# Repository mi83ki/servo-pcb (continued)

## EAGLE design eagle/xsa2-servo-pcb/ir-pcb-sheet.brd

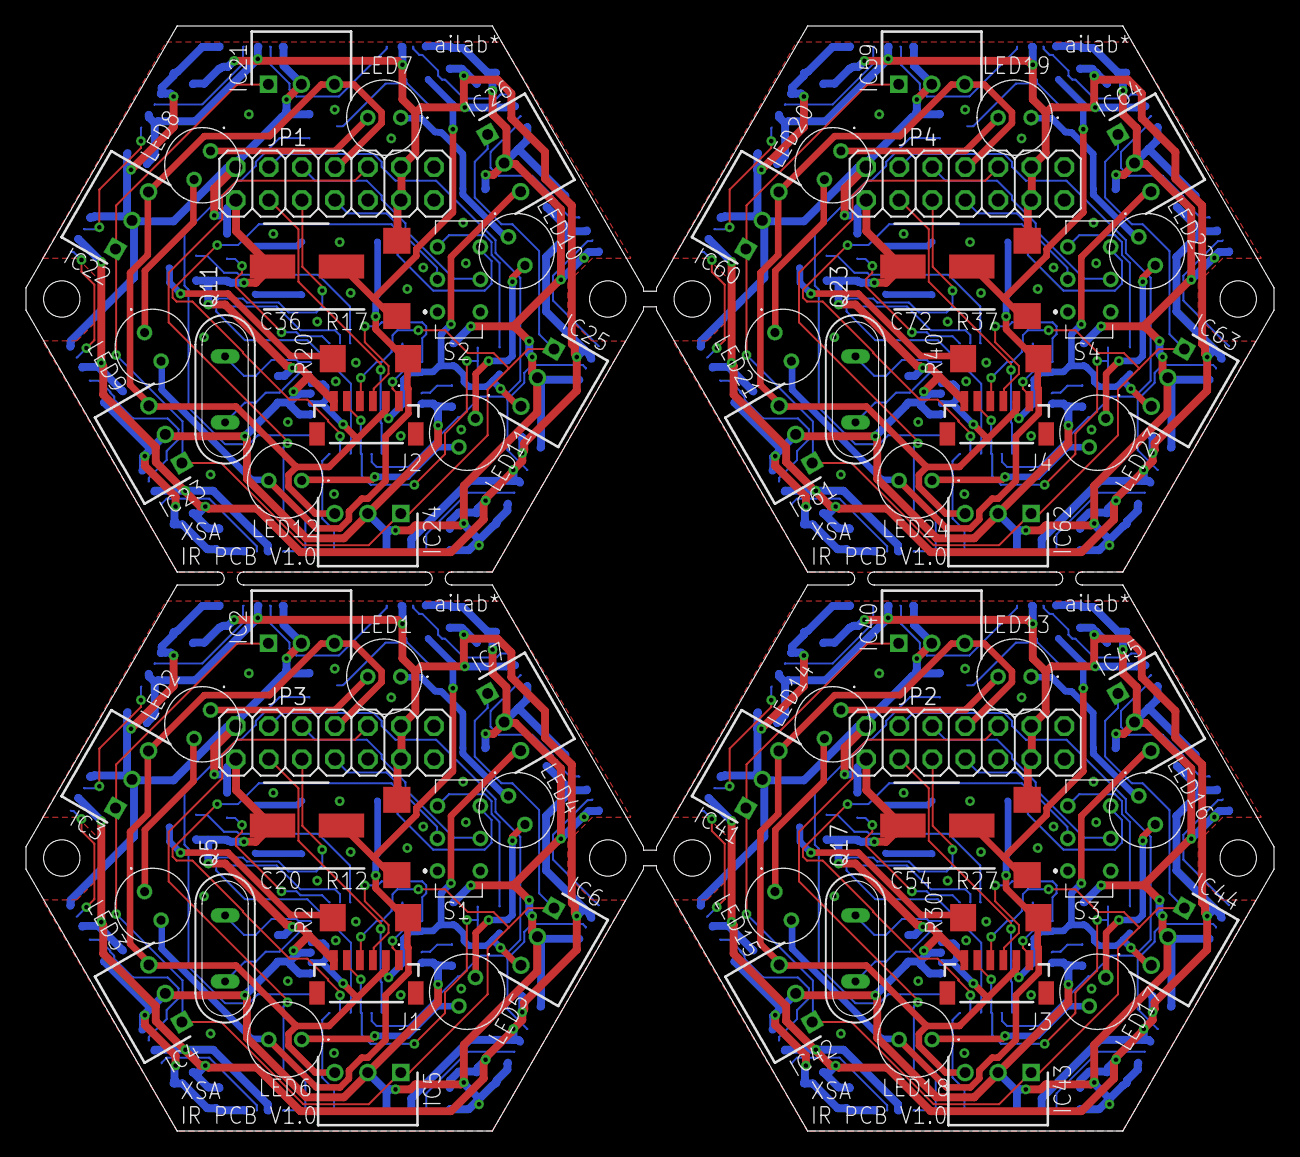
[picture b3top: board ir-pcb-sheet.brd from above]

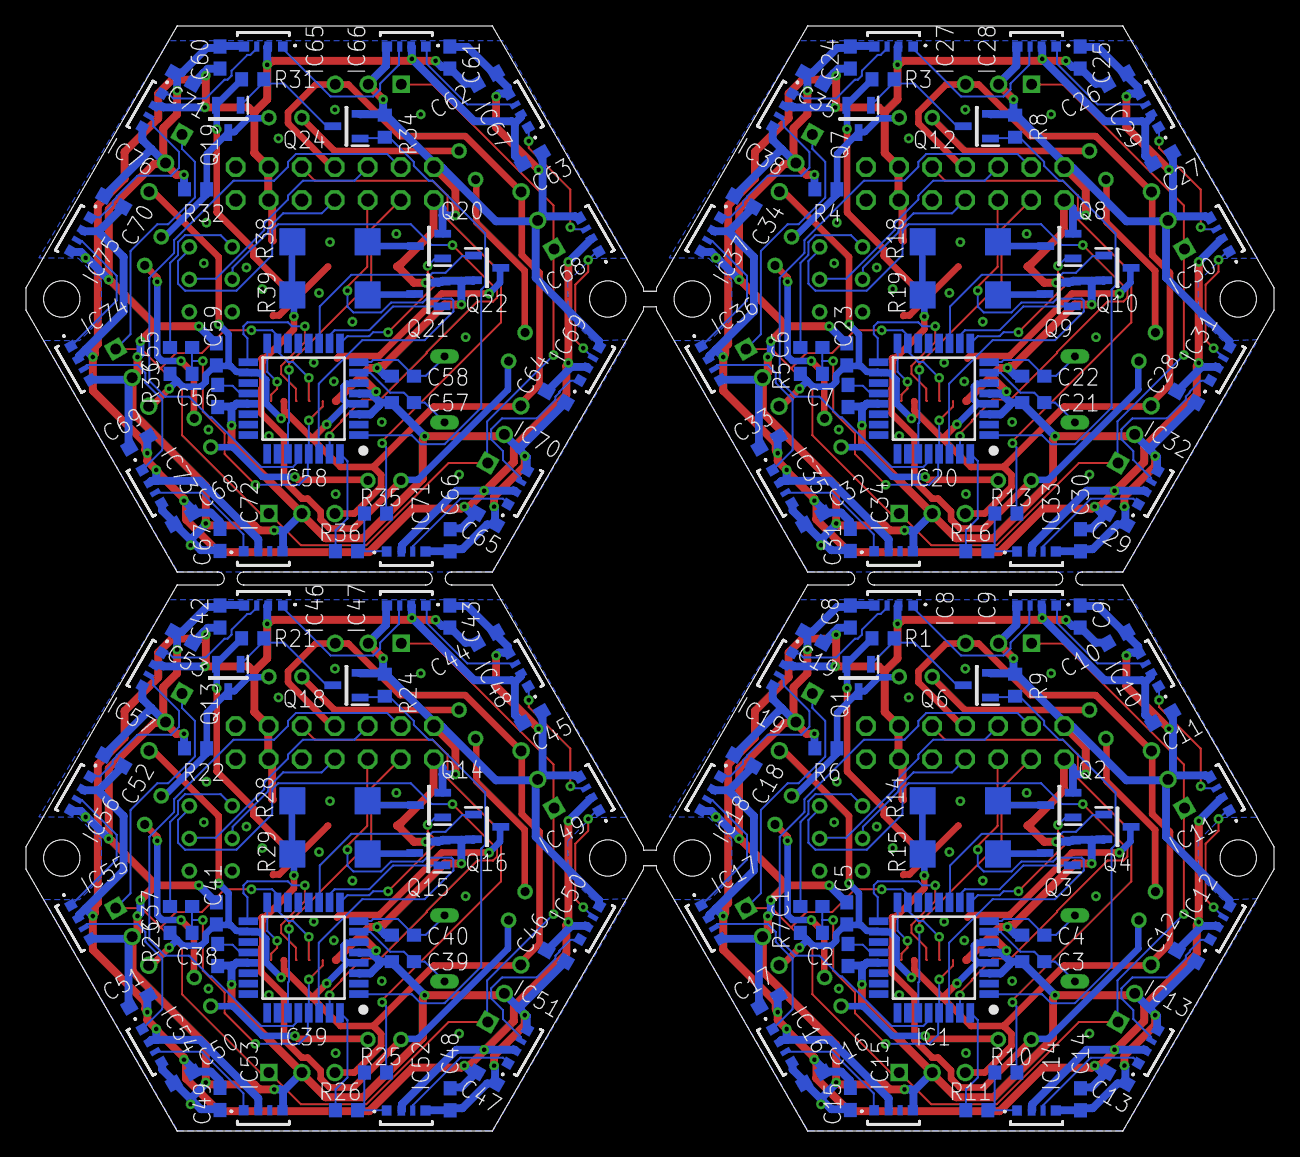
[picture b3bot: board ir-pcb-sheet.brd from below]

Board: 2 copper layers, 96.0 x 85.0 mm, 248 parts (172 on the bottom side), 184 nets.

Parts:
C1, C2, C5, C6, C7, C8, C9, C10, C11, C12, C13, C14, C15, C16, C17, C18, C19, C23, C24, C25, C26, C27, C28, C29, C30, C31, C32, C33, C34, C35, C37, C38, C41, C42, C43, C44, C45, C46, C47, C48, C49, C50, C51, C52, C53, C55, C56, C59, C60, C61, C62, C63, C64, C65, C66, C67, C68, C69, C70, C71: 0.1u; C0603
C3, C4, C21, C22, C39, C40, C57, C58: 22p; C0603
C20, C36, C54, C72: 25PFV100M6.3X8; CAPAE660X800N
IC1, IC20, IC39, IC58: ATMEGA328P-AU; QFP80P900X900X120-32N
IC2, IC3, IC4, IC5, IC6, IC7, IC21, IC22, IC23, IC24, IC25, IC26, IC40, IC41, IC42, IC43, IC44, IC45, IC59, IC60, IC61, IC62, IC63, IC64: PL-IRM0101; TO254P525X740X825-3P
IC8, IC9, IC10, IC11, IC12, IC13, IC14, IC15, IC16, IC17, IC18, IC19, IC27, IC28, IC29, IC30, IC31, IC32, IC33, IC34, IC35, IC36, IC37, IC38, IC46, IC47, IC48, IC49, IC50, IC51, IC52, IC53, IC54, IC55, IC56, IC57, IC65, IC66, IC67, IC68, IC69, IC70, IC71, IC72, IC73, IC74, IC75, IC76: SK6812_SIDE; SK6812SIDE
J1, J2, J3, J4: BM06B-SRSS-TBT_LF__SN_; BM06BSRSSTBTLFSN
JP1, JP2, JP3, JP4: Stacking Connector; 2X07
LED1, LED2, LED3, LED4, LED5, LED6, LED7, LED8, LED9, LED10, LED11, LED12, LED13, LED14, LED15, LED16, LED17, LED18, LED19, LED20, LED21, LED22, LED23, LED24: OSI5FU5111C-40; OSI5FU5111C40
Q1, Q7, Q13, Q19: IRLML6402; SOT95P237X112-3N
Q2, Q3, Q4, Q6, Q8, Q9, Q10, Q12, Q14, Q15, Q16, Q18, Q20, Q21, Q22, Q24: IRFML8244; SOT95P237X112-3N
Q5, Q11, Q17, Q23: 8MHz; QS
R1, R3, R4, R6, R8, R9, R21, R22, R24, R31, R32, R34: 1k; R0603
R2, R20, R30, R40: 39; R2512W
R5, R7, R23, R33: 10k; R0603
R10, R11, R13, R16, R25, R26, R35, R36: 0; R0603
R12, R17, R27, R37: 1; R2512W
R14, R18, R28, R38: 2; R2512W
R15, R19, R29, R39: 10; R2512W
S1, S2, S3, S4: IS-2235; IS2235

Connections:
+3V1: C23.2, IC20.4, IC20.6, IC20.18, IC21.3, IC22.3, IC23.3, IC24.3, IC25.3, IC26.3, J2.2, JP1.8, R5.1
+3V2: C41.2, IC39.4, IC39.6, IC39.18, IC40.3, IC41.3, IC42.3, IC43.3, IC44.3, IC45.3, J3.2, JP2.8, R23.1
+3V3: C5.2, IC1.4, IC1.6, IC1.18, IC2.3, IC3.3, IC4.3, IC5.3, IC6.3, IC7.3, J1.2, JP3.8, R7.1
+3V4: C59.2, IC58.4, IC58.6, IC58.18, IC59.3, IC60.3, IC61.3, IC62.3, IC63.3, IC64.3, J4.2, JP4.8, R33.1
GND: C2.1, C3.1, C4.1, C5.1, C8.1, C9.1, C10.1, C11.1, C12.1, C13.1, C14.1, C15.1, C16.1, C17.1, C18.1, C19.1, C20.2, IC1.3, IC1.5, IC1.21, IC2.2, IC3.2, IC4.2, IC5.2, IC6.2, IC7.2, IC8.4, IC9.4, IC10.4, IC11.4, IC12.4, IC13.4, IC14.4, IC15.4, IC16.4, IC17.4, IC18.4, IC19.4, J1.6, JP3.1, JP3.2, Q2.2, Q3.2, Q4.2, Q6.2, R6.1, R9.1
GND1: C7.1, C21.1, C22.1, C23.1, C24.1, C25.1, C26.1, C27.1, C28.1, C29.1, C30.1, C31.1, C32.1, C33.1, C34.1, C35.1, C36.2, IC20.3, IC20.5, IC20.21, IC21.2, IC22.2, IC23.2, IC24.2, IC25.2, IC26.2, IC27.4, IC28.4, IC29.4, IC30.4, IC31.4, IC32.4, IC33.4, IC34.4, IC35.4, IC36.4, IC37.4, IC38.4, J2.6, JP1.1, JP1.2, Q8.2, Q9.2, Q10.2, Q12.2, R4.1, R8.1
GND2: C38.1, C39.1, C40.1, C41.1, C42.1, C43.1, C44.1, C45.1, C46.1, C47.1, C48.1, C49.1, C50.1, C51.1, C52.1, C53.1, C54.2, IC39.3, IC39.5, IC39.21, IC40.2, IC41.2, IC42.2, IC43.2, IC44.2, IC45.2, IC46.4, IC47.4, IC48.4, IC49.4, IC50.4, IC51.4, IC52.4, IC53.4, IC54.4, IC55.4, IC56.4, IC57.4, J3.6, JP2.1, JP2.2, Q14.2, Q15.2, Q16.2, Q18.2, R22.1, R24.1
GND3: C56.1, C57.1, C58.1, C59.1, C60.1, C61.1, C62.1, C63.1, C64.1, C65.1, C66.1, C67.1, C68.1, C69.1, C70.1, C71.1, C72.2, IC58.3, IC58.5, IC58.21, IC59.2, IC60.2, IC61.2, IC62.2, IC63.2, IC64.2, IC65.4, IC66.4, IC67.4, IC68.4, IC69.4, IC70.4, IC71.4, IC72.4, IC73.4, IC74.4, IC75.4, IC76.4, J4.6, JP4.1, JP4.2, Q20.2, Q21.2, Q22.2, Q24.2, R32.1, R34.1
LED1: LED1.1, LED4.1, Q1.3, R6.2
LED2: C20.1, Q1.2, R1.1, R12.1
LED3: LED4.2, LED5.1
LED4: LED1.2, LED2.1
LED5: LED5.2, LED6.1
LED6: LED2.2, LED3.1
LED7: LED3.2, LED6.2, R2.2, R14.2, R15.2
LED8: Q2.3, R14.1
LED9: Q3.3, R15.1
LED10: Q4.3, R2.1
LED11: LED7.2, LED8.1
LED12: LED8.2, LED9.1
LED13: LED10.2, LED11.1
LED14: LED11.2, LED12.1
LED15: LED7.1, LED10.1, Q7.3, R4.2
LED16: LED9.2, LED12.2, R18.2, R19.2, R20.2
LED17: Q8.3, R18.1
LED18: Q9.3, R19.1
LED19: Q10.3, R20.1
LED20: C36.1, Q7.2, R3.1, R17.1
LED21: LED13.2, LED14.1
LED22: LED14.2, LED15.1
LED23: LED16.2, LED17.1
LED24: LED17.2, LED18.1
LED25: LED13.1, LED16.1, Q13.3, R22.2
LED26: LED15.2, LED18.2, R28.2, R29.2, R30.2
LED27: Q14.3, R28.1
LED28: Q15.3, R29.1
LED29: Q16.3, R30.1
LED30: C54.1, Q13.2, R21.1, R27.1
LED31: LED19.2, LED20.1
LED32: LED20.2, LED21.1
LED33: LED22.2, LED23.1
LED34: LED23.2, LED24.1
LED35: LED19.1, LED22.1, Q19.3, R32.2
LED36: LED21.2, LED24.2, R38.2, R39.2, R40.2
LED37: Q20.3, R38.1
LED38: Q21.3, R39.1
LED39: Q22.3, R40.1
LED40: C72.1, Q19.2, R31.1, R37.1
unnamed: IC1.16, J1.1
unnamed: Q1.1, Q6.3, R1.2
unnamed: JP3.6, S1.5
unnamed: IC20.17, J2.3
unnamed: IC1.17, J1.3
unnamed: IC20.16, J2.1
unnamed: IC20.1, Q12.1, R8.2
unnamed: IC20.9, Q8.1
unnamed: IC20.10, Q9.1
unnamed: IC1.1, Q6.1, R9.2
unnamed: IC8.1, IC9.3
unnamed: IC20.11, Q10.1
unnamed: C2.2, IC1.20
unnamed: JP3.7, S1.2
unnamed: IC20.28, JP1.4
unnamed: IC20.30, JP1.5
unnamed: C7.2, IC20.20
unnamed: IC1.9, Q2.1
unnamed: IC1.10, Q3.1
unnamed: IC1.11, Q4.1
unnamed: IC1.28, JP3.4
unnamed: C3.2, IC1.7, Q5.1
unnamed: IC1.30, JP3.5
unnamed: IC13.1, IC14.3
unnamed: C1.2, IC1.29, J1.5, R7.2
unnamed: C4.2, IC1.8, Q5.2
unnamed: C21.2, IC20.7, Q11.1
unnamed: C1.1, S1.3
unnamed: IC1.31, S1.6
unnamed: IC1.27, JP3.3
unnamed: IC12.1, IC13.3
unnamed: IC11.1, IC12.3
unnamed: IC10.1, IC11.3
unnamed: IC9.1, IC10.3
unnamed: C22.2, IC20.8, Q11.2
unnamed: IC8.3, IC19.1
unnamed: IC18.1, IC19.3
unnamed: IC17.1, IC18.3
unnamed: IC16.1, IC17.3
unnamed: IC15.1, IC16.3
unnamed: IC1.15, IC2.1, IC3.1, IC4.1, IC5.1, IC6.1, IC7.1, J1.4
unnamed: JP3.10, R10.2
unnamed: IC1.32, R11.2
unnamed: IC14.1, R10.1, R11.1
unnamed: C6.2, IC20.29, J2.5, R5.2
unnamed: C6.1, S2.3
unnamed: Q7.1, Q12.3, R3.2
unnamed: IC20.27, JP1.3
unnamed: JP1.6, S2.5
unnamed: JP1.7, S2.2
unnamed: IC20.31, S2.6
unnamed: JP1.10, R13.2
unnamed: IC20.32, R16.2
unnamed: IC20.15, IC21.1, IC22.1, IC23.1, IC24.1, IC25.1, IC26.1, J2.4
unnamed: IC32.1, IC33.3
unnamed: IC31.1, IC32.3
unnamed: IC30.1, IC31.3
unnamed: IC29.1, IC30.3
unnamed: IC28.1, IC29.3
unnamed: IC33.1, R13.1, R16.1
unnamed: IC27.3, IC38.1
unnamed: IC37.1, IC38.3
unnamed: IC36.1, IC37.3
unnamed: IC35.1, IC36.3
unnamed: IC34.1, IC35.3
unnamed: IC27.1, IC28.3
unnamed: IC39.17, J3.3
unnamed: IC39.16, J3.1
unnamed: IC39.1, Q18.1, R24.2
unnamed: IC39.9, Q14.1
unnamed: IC39.10, Q15.1
unnamed: IC39.11, Q16.1
unnamed: IC39.28, JP2.4
unnamed: IC39.30, JP2.5
unnamed: C38.2, IC39.20
unnamed: C39.2, IC39.7, Q17.1
unnamed: C40.2, IC39.8, Q17.2
unnamed: C37.2, IC39.29, J3.5, R23.2
unnamed: C37.1, S3.3
unnamed: Q13.1, Q18.3, R21.2
unnamed: IC39.27, JP2.3
unnamed: JP2.6, S3.5
unnamed: JP2.7, S3.2
unnamed: IC39.31, S3.6
unnamed: JP2.10, R25.2
unnamed: IC39.32, R26.2
unnamed: IC39.15, IC40.1, IC41.1, IC42.1, IC43.1, IC44.1, IC45.1, J3.4
unnamed: IC51.1, IC52.3
unnamed: IC50.1, IC51.3
unnamed: IC49.1, IC50.3
unnamed: IC48.1, IC49.3
unnamed: IC47.1, IC48.3
unnamed: IC52.1, R25.1, R26.1
unnamed: IC46.3, IC57.1
unnamed: IC56.1, IC57.3
unnamed: IC55.1, IC56.3
unnamed: IC54.1, IC55.3
unnamed: IC53.1, IC54.3
unnamed: IC46.1, IC47.3
unnamed: IC58.17, J4.3
unnamed: IC58.16, J4.1
unnamed: IC58.1, Q24.1, R34.2
unnamed: IC58.9, Q20.1
unnamed: IC58.10, Q21.1
unnamed: IC58.11, Q22.1
unnamed: IC58.28, JP4.4
unnamed: IC58.30, JP4.5
unnamed: C56.2, IC58.20
unnamed: C57.2, IC58.7, Q23.1
unnamed: C58.2, IC58.8, Q23.2
unnamed: C55.2, IC58.29, J4.5, R33.2
unnamed: C55.1, S4.3
unnamed: Q19.1, Q24.3, R31.2
unnamed: IC58.27, JP4.3
unnamed: JP4.6, S4.5
unnamed: JP4.7, S4.2
unnamed: IC58.31, S4.6
unnamed: JP4.10, R35.2
unnamed: IC58.32, R36.2
unnamed: IC58.15, IC59.1, IC60.1, IC61.1, IC62.1, IC63.1, IC64.1, J4.4
unnamed: IC70.1, IC71.3
unnamed: IC69.1, IC70.3
unnamed: IC68.1, IC69.3
unnamed: IC67.1, IC68.3
unnamed: IC66.1, IC67.3
unnamed: IC71.1, R35.1, R36.1
unnamed: IC65.3, IC76.1
unnamed: IC75.1, IC76.3
unnamed: IC74.1, IC75.3
unnamed: IC73.1, IC74.3
unnamed: IC72.1, IC73.3
unnamed: IC65.1, IC66.3
VDD: C8.2, C9.2, C10.2, C11.2, C12.2, C13.2, C14.2, C15.2, C16.2, C17.2, C18.2, C19.2, IC8.2, IC9.2, IC10.2, IC11.2, IC12.2, IC13.2, IC14.2, IC15.2, IC16.2, IC17.2, IC18.2, IC19.2, JP3.11, JP3.12, R12.2
VDD1: C24.2, C25.2, C26.2, C27.2, C28.2, C29.2, C30.2, C31.2, C32.2, C33.2, C34.2, C35.2, IC27.2, IC28.2, IC29.2, IC30.2, IC31.2, IC32.2, IC33.2, IC34.2, IC35.2, IC36.2, IC37.2, IC38.2, JP1.11, JP1.12, R17.2
VDD2: C42.2, C43.2, C44.2, C45.2, C46.2, C47.2, C48.2, C49.2, C50.2, C51.2, C52.2, C53.2, IC46.2, IC47.2, IC48.2, IC49.2, IC50.2, IC51.2, IC52.2, IC53.2, IC54.2, IC55.2, IC56.2, IC57.2, JP2.11, JP2.12, R27.2
VDD3: C60.2, C61.2, C62.2, C63.2, C64.2, C65.2, C66.2, C67.2, C68.2, C69.2, C70.2, C71.2, IC65.2, IC66.2, IC67.2, IC68.2, IC69.2, IC70.2, IC71.2, IC72.2, IC73.2, IC74.2, IC75.2, IC76.2, JP4.11, JP4.12, R37.2

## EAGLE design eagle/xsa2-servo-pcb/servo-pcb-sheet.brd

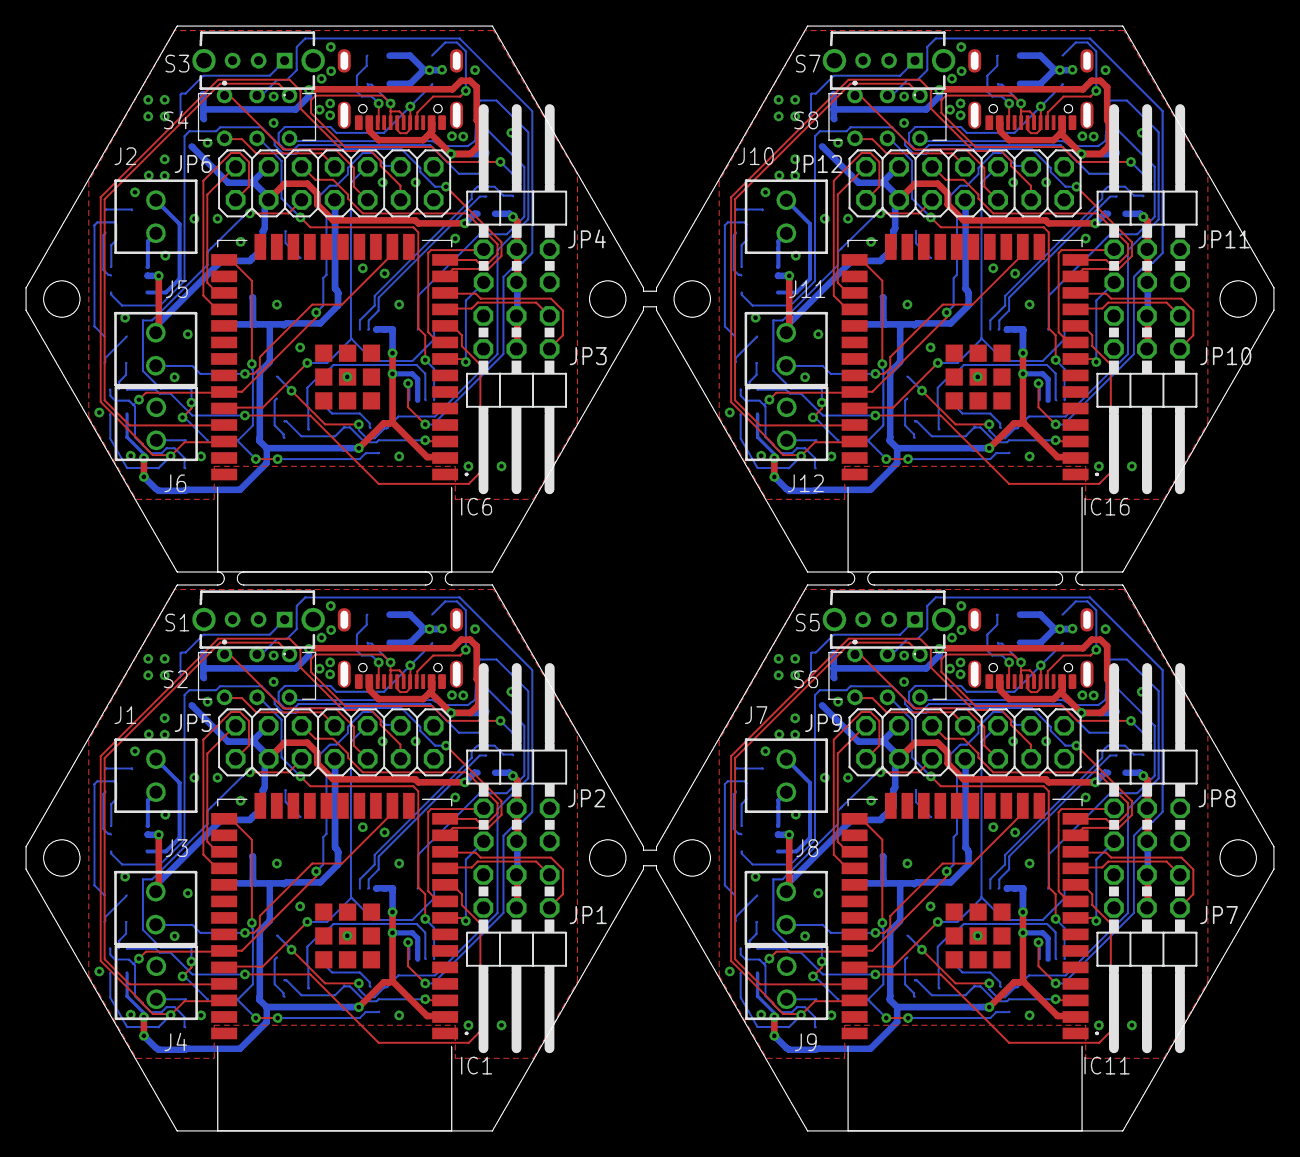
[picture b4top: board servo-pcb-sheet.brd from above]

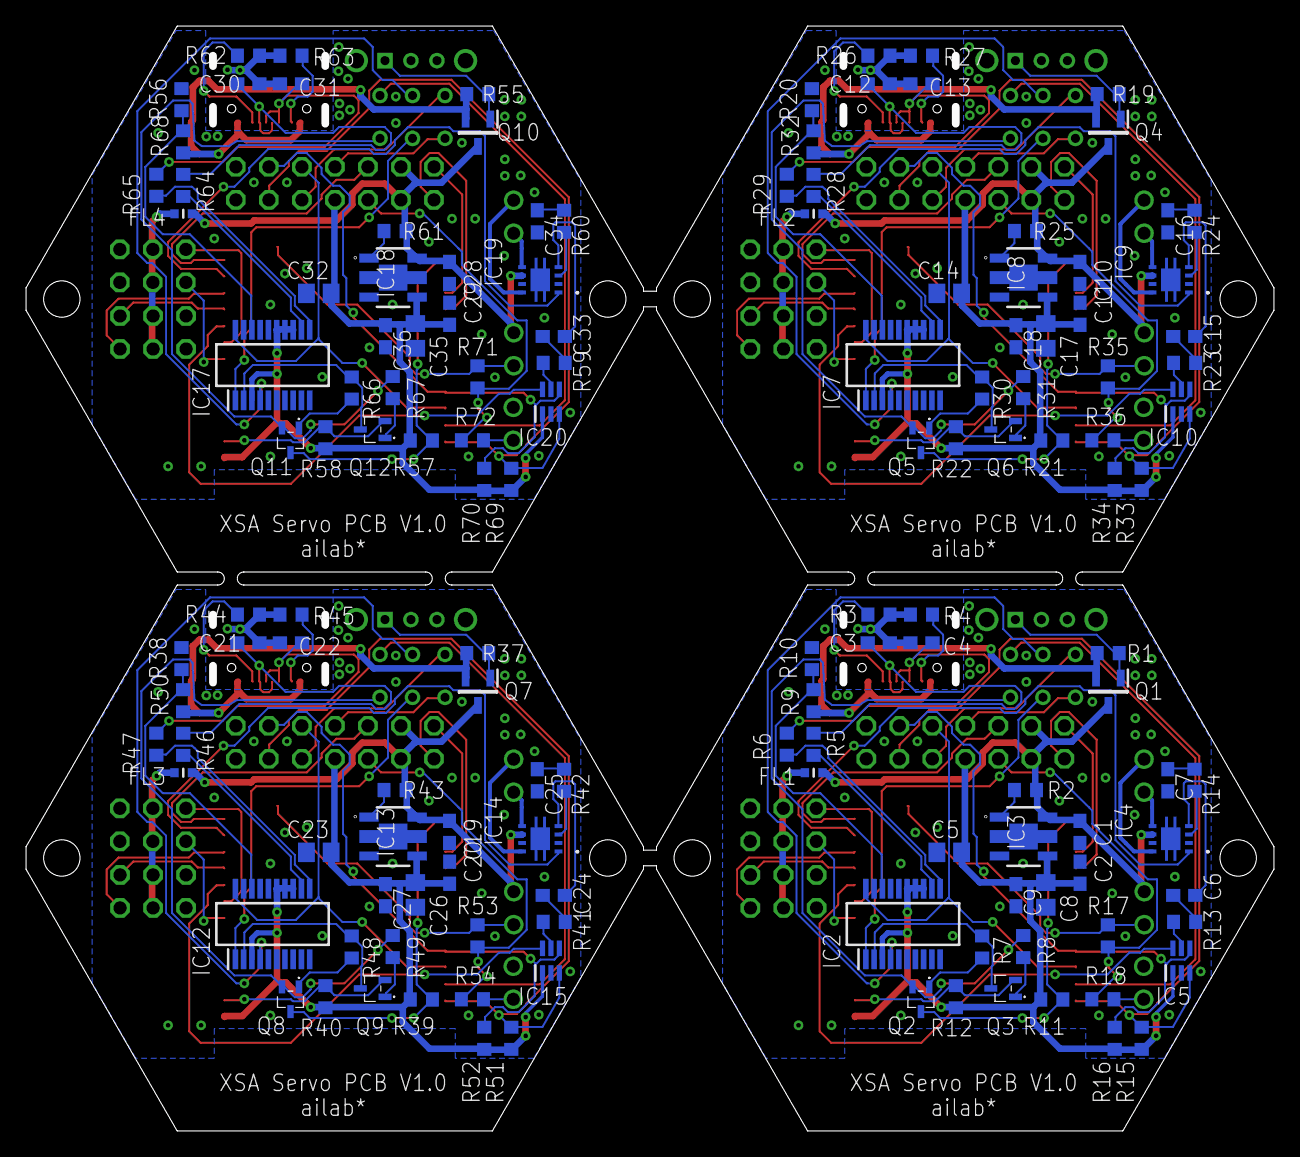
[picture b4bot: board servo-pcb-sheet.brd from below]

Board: 2 copper layers, 95.4 x 84.4 mm, 180 parts (140 on the bottom side), 188 nets.

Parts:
C1, C10, C19, C28: 0.33uF; C0603
C2, C6, C7, C11, C15, C16, C20, C24, C25, C29, C33, C34: 1uF; C0603
C3, C4, C12, C13, C21, C22, C30, C31: 39pF; C0603
C5, C8, C14, C17, C23, C26, C32, C35: 10uF; C0805
C9, C18, C27, C36: 0.01uF; C0603
FL1, FL2, FL3, FL4: BLM18PG121SN1D; BLM18AG102BH1D
IC1, IC6, IC11, IC16: ESP32-WROOM-32D__4MB_PS_; ESP32WROOM32D4MBPS
IC2, IC7, IC12, IC17: FT231XS-R; SOP64P599X175-20N
IC3, IC8, IC13, IC18: NJM2884U1-33-TE1; SOT-89-5-1
IC4, IC9, IC14, IC19: TPA2006D1DRBR
IC5, IC10, IC15, IC20: ISL90728UIE627Z-TK; SOT65P210X110-6N
J1, J2, J3, J4, J5, J6, J7, J8, J9, J10, J11, J12: WJEK254-2.54-02P-140-00A; WJEK25425402P14000A
JP1, JP3, JP7, JP10: SERVO1; 2X03/90
JP2, JP4, JP8, JP11: SERVO2; 2X03/90
JP5, JP6, JP9, JP12: 2X07
Q1, Q4, Q7, Q10: IRLML6402; SOT95P237X112-3N
Q2, Q3, Q5, Q6, Q8, Q9, Q11, Q12: 2SC2712-GR_F_; SSM3K7002CFULF
R1, R10, R11, R12, R19, R20, R21, R22, R37, R38, R39, R40, R55, R56, R57, R58: 10k; R0603
R2, R15, R16, R25, R33, R34, R43, R51, R52, R61, R69, R70: 1k; R0603
R3, R4, R9, R26, R27, R32, R44, R45, R50, R62, R63, R68: 4.7k; R0603
R5, R6, R28, R29, R46, R47, R64, R65: 27; R0603
R7, R8, R30, R31, R48, R49, R66, R67: 12k; R0603
R13, R14, R23, R24, R41, R42, R59, R60: 100k; R0603
R17, R18, R35, R36, R53, R54, R71, R72: 0; R0603
S1, S3, S5, S7: SK-12D11VG3; SK12D11VG3
S2, S4, S6, S8: IS-2235; IS2235
U$1, U$2, U$3, U$4: 5077CR-16-SMC2-BK-TR; 5077CR-16SMC2-BK-TR

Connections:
+3V1: C11.1, C14.1, C17.1, C18.1, IC6.2, IC7.3, IC7.13, IC7.14, IC7.15, IC8.4, IC10.1, JP6.8, R21.2, R22.2, R33.2, R34.2
+3V2: C20.1, C23.1, C26.1, C27.1, IC11.2, IC12.3, IC12.13, IC12.14, IC12.15, IC13.4, IC15.1, JP9.8, R39.2, R40.2, R51.2, R52.2
+3V3: C2.1, C5.1, C8.1, C9.1, IC1.2, IC2.3, IC2.13, IC2.14, IC2.15, IC3.4, IC5.1, JP5.8, R11.2, R12.2, R15.2, R16.2
+3V4: C29.1, C32.1, C35.1, C36.1, IC16.2, IC17.3, IC17.13, IC17.14, IC17.15, IC18.4, IC20.1, JP12.8, R57.2, R58.2, R69.2, R70.2
DTR: IC2.1, S2.5
DTR1: IC7.1, S4.5
DTR2: IC12.1, S6.5
DTR3: IC17.1, S8.5
GND: C1.2, C2.2, C3.2, C4.2, C5.2, C7.2, C8.2, C9.2, IC1.1, IC1.15, IC1.38, IC1.39, IC1.40, IC1.41, IC1.42, IC1.43, IC1.44, IC1.45, IC1.46, IC1.47, IC2.6, IC2.16, IC3.2, IC3.5, IC4.7, IC5.2, J4.2, JP1.5, JP1.6, JP2.5, JP2.6, JP5.1, JP5.2, R3.1, R4.1, R10.1, S1.2, S1.MH1, S1.MH2, U$1.A1,B12:GND, U$1.B1,A12:GND
GND1: C10.2, C11.2, C12.2, C13.2, C14.2, C16.2, C17.2, C18.2, IC6.1, IC6.15, IC6.38, IC6.39, IC6.40, IC6.41, IC6.42, IC6.43, IC6.44, IC6.45, IC6.46, IC6.47, IC7.6, IC7.16, IC8.2, IC8.5, IC9.7, IC10.2, J6.2, JP3.5, JP3.6, JP4.5, JP4.6, JP6.1, JP6.2, R20.1, R26.1, R27.1, S3.2, S3.MH1, S3.MH2, U$2.A1,B12:GND, U$2.B1,A12:GND
GND2: C19.2, C20.2, C21.2, C22.2, C23.2, C25.2, C26.2, C27.2, IC11.1, IC11.15, IC11.38, IC11.39, IC11.40, IC11.41, IC11.42, IC11.43, IC11.44, IC11.45, IC11.46, IC11.47, IC12.6, IC12.16, IC13.2, IC13.5, IC14.7, IC15.2, J9.2, JP7.5, JP7.6, JP8.5, JP8.6, JP9.1, JP9.2, R38.1, R44.1, R45.1, S5.2, S5.MH1, S5.MH2, U$3.A1,B12:GND, U$3.B1,A12:GND
GND3: C28.2, C29.2, C30.2, C31.2, C32.2, C34.2, C35.2, C36.2, IC16.1, IC16.15, IC16.38, IC16.39, IC16.40, IC16.41, IC16.42, IC16.43, IC16.44, IC16.45, IC16.46, IC16.47, IC17.6, IC17.16, IC18.2, IC18.5, IC19.7, IC20.2, J12.2, JP10.5, JP10.6, JP11.5, JP11.6, JP12.1, JP12.2, R56.1, R62.1, R63.1, S7.2, S7.MH1, S7.MH2, U$4.A1,B12:GND, U$4.B1,A12:GND
IO1: IC6.14, JP6.9
IO2: JP6.10, R35.2, R36.2
IO3: IC11.14, JP9.9
IO4: JP9.10, R53.2, R54.2
IO5: IC16.14, JP12.9
IO6: JP12.10, R71.2, R72.2
IO12: IC1.14, JP5.9
IO13: JP5.10, R17.2, R18.2
unnamed: C4.1, R6.1, U$1.A6:DP1, U$1.B6:DP2
unnamed: Q1.1, R1.1, S1.1
unnamed: IC3.1, R2.2
unnamed: IC1.28, JP5.14
unnamed: C3.1, R5.1, U$1.A7:DN1, U$1.B7:DN2
unnamed: IC1.34, IC2.20, JP5.5
unnamed: IC2.12, R5.2
unnamed: IC2.11, R6.2
unnamed: IC2.2, Q3.3, R7.1
unnamed: Q2.1, R7.2
unnamed: Q2.2, R8.1, S2.6
unnamed: Q3.1, R8.2
unnamed: IC2.18, R9.1, R10.2
unnamed: IC1.3, Q3.2, R12.1
unnamed: IC1.25, Q2.3, R11.1
unnamed: IC1.35, S2.3
unnamed: JP5.7, S2.4
unnamed: IC5.5, R13.1
unnamed: C6.1, R13.2
unnamed: C6.2, IC4.4
unnamed: IC4.3, R14.2
unnamed: C7.1, R14.1
unnamed: IC1.36, IC5.3, JP5.4, R15.1
unnamed: IC1.33, IC5.4, JP5.3, R16.1
unnamed: IC1.13, IC4.1
unnamed: IC4.8, J1.1
unnamed: IC4.5, J1.2
unnamed: IC1.10, IC5.6
unnamed: IC1.16, J3.1, R17.1
unnamed: IC1.11, JP1.1
unnamed: IC1.12, JP1.2
unnamed: IC1.8, JP2.1
unnamed: IC1.9, JP2.2
unnamed: IC1.27, JP5.13
unnamed: R4.2, U$1.B5:CC2
unnamed: J4.1, R18.1
unnamed: Q4.1, R19.1, S3.1
unnamed: FL1.1, JP1.3, JP1.4, JP2.3, JP2.4
unnamed: IC8.1, R25.2
unnamed: C13.1, R29.1, U$2.A6:DP1, U$2.B6:DP2
unnamed: JP5.6, S2.1
unnamed: R3.2, U$1.A5:CC1
unnamed: C12.1, R28.1, U$2.A7:DN1, U$2.B7:DN2
unnamed: IC7.12, R28.2
unnamed: IC7.11, R29.2
unnamed: IC7.2, Q6.3, R30.1
unnamed: Q5.1, R30.2
unnamed: Q5.2, R31.1, S4.6
unnamed: Q6.1, R31.2
unnamed: IC7.18, R20.2, R32.1
unnamed: IC6.3, Q6.2, R22.1
unnamed: IC6.25, Q5.3, R21.1
unnamed: IC6.35, S4.3
unnamed: IC10.5, R23.1
unnamed: C15.1, R23.2
unnamed: C15.2, IC9.4
unnamed: IC9.3, R24.2
unnamed: C16.1, R24.1
unnamed: IC6.36, IC10.3, JP6.4, R33.1
unnamed: IC6.33, IC10.4, JP6.3, R34.1
unnamed: IC6.13, IC9.1
unnamed: IC9.8, J2.1
unnamed: IC9.5, J2.2
unnamed: IC6.10, IC10.6
unnamed: IC6.11, JP3.1
unnamed: IC6.12, JP3.2
unnamed: IC6.8, JP4.1
unnamed: IC6.9, JP4.2
unnamed: IC6.27, JP6.13
unnamed: JP6.7, S4.4
unnamed: JP6.6, S4.1
unnamed: R27.2, U$2.B5:CC2
unnamed: R26.2, U$2.A5:CC1
unnamed: IC6.28, JP6.14
unnamed: IC6.34, IC7.20, JP6.5
unnamed: IC6.16, J5.1, R35.1
unnamed: J6.1, R36.1
unnamed: FL2.1, JP3.3, JP3.4, JP4.3, JP4.4
unnamed: Q7.1, R37.1, S5.1
unnamed: IC13.1, R43.2
unnamed: C22.1, R47.1, U$3.A6:DP1, U$3.B6:DP2
unnamed: C21.1, R46.1, U$3.A7:DN1, U$3.B7:DN2
unnamed: IC12.12, R46.2
unnamed: IC12.11, R47.2
unnamed: IC12.2, Q9.3, R48.1
unnamed: Q8.1, R48.2
unnamed: Q8.2, R49.1, S6.6
unnamed: Q9.1, R49.2
unnamed: IC12.18, R38.2, R50.1
unnamed: IC11.3, Q9.2, R40.1
unnamed: IC11.25, Q8.3, R39.1
unnamed: IC11.35, S6.3
unnamed: IC15.5, R41.1
unnamed: C24.1, R41.2
unnamed: C24.2, IC14.4
unnamed: IC14.3, R42.2
unnamed: C25.1, R42.1
unnamed: IC11.36, IC15.3, JP9.4, R51.1
unnamed: IC11.33, IC15.4, JP9.3, R52.1
unnamed: IC11.13, IC14.1
unnamed: IC14.8, J7.1
unnamed: IC14.5, J7.2
unnamed: IC11.10, IC15.6
unnamed: IC11.11, JP7.1
unnamed: IC11.12, JP7.2
unnamed: IC11.8, JP8.1
unnamed: IC11.9, JP8.2
unnamed: IC11.27, JP9.13
unnamed: JP9.7, S6.4
unnamed: JP9.6, S6.1
unnamed: R45.2, U$3.B5:CC2
unnamed: R44.2, U$3.A5:CC1
unnamed: IC11.28, JP9.14
unnamed: IC11.34, IC12.20, JP9.5
unnamed: IC11.16, J8.1, R53.1
unnamed: J9.1, R54.1
unnamed: FL3.1, JP7.3, JP7.4, JP8.3, JP8.4
unnamed: Q10.1, R55.1, S7.1
unnamed: IC18.1, R61.2
unnamed: C31.1, R65.1, U$4.A6:DP1, U$4.B6:DP2
unnamed: C30.1, R64.1, U$4.A7:DN1, U$4.B7:DN2
unnamed: IC17.12, R64.2
unnamed: IC17.11, R65.2
unnamed: IC17.2, Q12.3, R66.1
unnamed: Q11.1, R66.2
unnamed: Q11.2, R67.1, S8.6
unnamed: Q12.1, R67.2
unnamed: IC17.18, R56.2, R68.1
unnamed: IC16.3, Q12.2, R58.1
unnamed: IC16.25, Q11.3, R57.1
unnamed: IC16.35, S8.3
unnamed: IC20.5, R59.1
unnamed: C33.1, R59.2
unnamed: C33.2, IC19.4
unnamed: IC19.3, R60.2
unnamed: C34.1, R60.1
unnamed: IC16.36, IC20.3, JP12.4, R69.1
unnamed: IC16.33, IC20.4, JP12.3, R70.1
unnamed: IC16.13, IC19.1
unnamed: IC19.8, J10.1
unnamed: IC19.5, J10.2
unnamed: IC16.10, IC20.6
unnamed: IC16.11, JP10.1
unnamed: IC16.12, JP10.2
unnamed: IC16.8, JP11.1
unnamed: IC16.9, JP11.2
unnamed: IC16.27, JP12.13
unnamed: JP12.7, S8.4
unnamed: JP12.6, S8.1
unnamed: R63.2, U$4.B5:CC2
unnamed: R62.2, U$4.A5:CC1
unnamed: IC16.28, JP12.14
unnamed: IC16.34, IC17.20, JP12.5
unnamed: IC16.16, J11.1, R71.1
unnamed: J12.1, R72.1
unnamed: FL4.1, JP10.3, JP10.4, JP11.3, JP11.4
RXD: IC2.4, S2.2
RXD1: IC7.4, S4.2
RXD2: IC12.4, S6.2
RXD3: IC17.4, S8.2
VCC: Q1.2, R1.2, R9.2, U$1.A4,B9:V_BUS, U$1.B4,A9:VBUS
VCC1: Q4.2, R19.2, R32.2, U$2.A4,B9:V_BUS, U$2.B4,A9:VBUS
VCC2: Q7.2, R37.2, R50.2, U$3.A4,B9:V_BUS, U$3.B4,A9:VBUS
VCC3: Q10.2, R55.2, R68.2, U$4.A4,B9:V_BUS, U$4.B4,A9:VBUS
VDD: C1.1, FL1.2, IC3.6, IC4.6, J3.2, JP5.11, JP5.12, Q1.3, R2.1
VDD1: C10.1, FL2.2, IC8.6, IC9.6, J5.2, JP6.11, JP6.12, Q4.3, R25.1
VDD2: C19.1, FL3.2, IC13.6, IC14.6, J8.2, JP9.11, JP9.12, Q7.3, R43.1
VDD3: C28.1, FL4.2, IC18.6, IC19.6, J11.2, JP12.11, JP12.12, Q10.3, R61.1

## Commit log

2022-07-23 eagleプロジェクトの追加
2022-08-06 [README] 資料の更新
2022-08-06 [eagle] 部品追加
2022-08-06 [eagle] 基板設計追加
2022-08-07 [eagle] 回路追加
2022-08-07 [eagle] AVRの赤外受光ピンを変更
2022-08-07 [eagle] 赤外発光部のPMOSにNMOSを追加
2022-08-07 [eagle] 回路図更新
2022-08-08 [eagle] 連結コネクタのピン数を増加
2022-09-03 [eagle] パターン追加
2022-09-03 [dxf] 基板外形図の追加
2022-10-22 [eagle] メイン基板パターン設計完了
2022-11-20 [dxf] IR基板のDXFデータを追加
2022-11-20 [eagle] IR基板のパターン設計
2022-11-27 [eagle] サーボ基板の更新
2022-11-27 [eagle] サーボ基板完成
2022-12-30 [eagle] サーボ基板の面付け
2022-12-30 [gerberdata] 手配用のガーバーデータ作成
2023-01-09 [eagle] IR基板の更新
2023-01-09 [eagle] IR基板の面付け
2023-01-09 [eagle] IR基板のガーバーデータ
2023-03-19 [gitignore] .gitignoreを追加
2023-03-20 [src] ArduinoCommonライブラリを追加
2023-03-20 [src] サーボ駆動プログラムの新規追加
